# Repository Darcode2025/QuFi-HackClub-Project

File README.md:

# QuFi-HackClub-Project
This is a macropad specifically designed for excel shortcuts for accounting in public companies and private companies. Its more relevant for public companies who have to track and show certain data to shareholders.

# QuFi

### **A custom macropad that simplifies accounting and financial analysis.**
---

# What Is This? 

**QuFi** is a macropad that brings some of the most commonly used financial formulas into excel with no technical experience
required. It uniquely offers both commonly used preloaded formulas, as well as customizable layers in a library of financial formulas or you can bring your own formulas! 

- **GAAP Accounting Formulas:** QuFi Comes preloaded with 27 GAAP Accounting formulas with everything from calculating assets to Income Calculations
- **Full Customizable Library:** I'm currently working on a libarary to bring almost any excel accounting or corporate finance formula to QuFi which will allow users the change their configurationa and quick formulas.
- **Custom Formulas:** I'm working on documentation for users to create their own formulas either by themselves or using AI to apply to QuFi.

## Key Layout

| Key | Action | Shortcut Sent |
|-----|--------|---------------|
| 1 | Accounting equation check (should equal 0) | =Assets-(Liabilities+Equity) |
| 2 |Gross profit | =Revenue-COGS |
| 3 | Net income | 	=Revenue-Expenses |
| 4 | Gross margin % | =(Revenue-COGS)/Revenue |
| 5 | Working capital | =CurrentAssets-CurrentLiabilities |
| 6 | Current ratio| =(Cash+AR+Securities)/CurrentLiabilities |
| 7 | Quick ratio | 	=Revenue-Expenses |
| 8 | Debt-to-equity | =TotalLiabilities/TotalEquity |
| 9 | Straight-line depreciation | =SLN(Cost,Salvage,Life) |
---

# How To Use It

1. Plug it into your computer via USB-C.
2. Firmware is being developed
3. Open Excel and press any key.
4. Command changed in firmware are being developed.
5. To directly select numbers used in the formula, click equals in the cell which the desired output should reside in, then click on all the relevant data in order they show up in the equation, then click the key on QuFi

---

# Why I Made This

My Parents are in corporate finance, and I suprisingly love investing and financial analysis. I see them every day using excel and related platforms and its genuinly a typing strain. I've personally used it many times as well 
and it is still efficient but it can be easier and quicker.

---

# Images

## Full 3D Model without keycaps and knob (Assembled)

## PCB

## Schematic

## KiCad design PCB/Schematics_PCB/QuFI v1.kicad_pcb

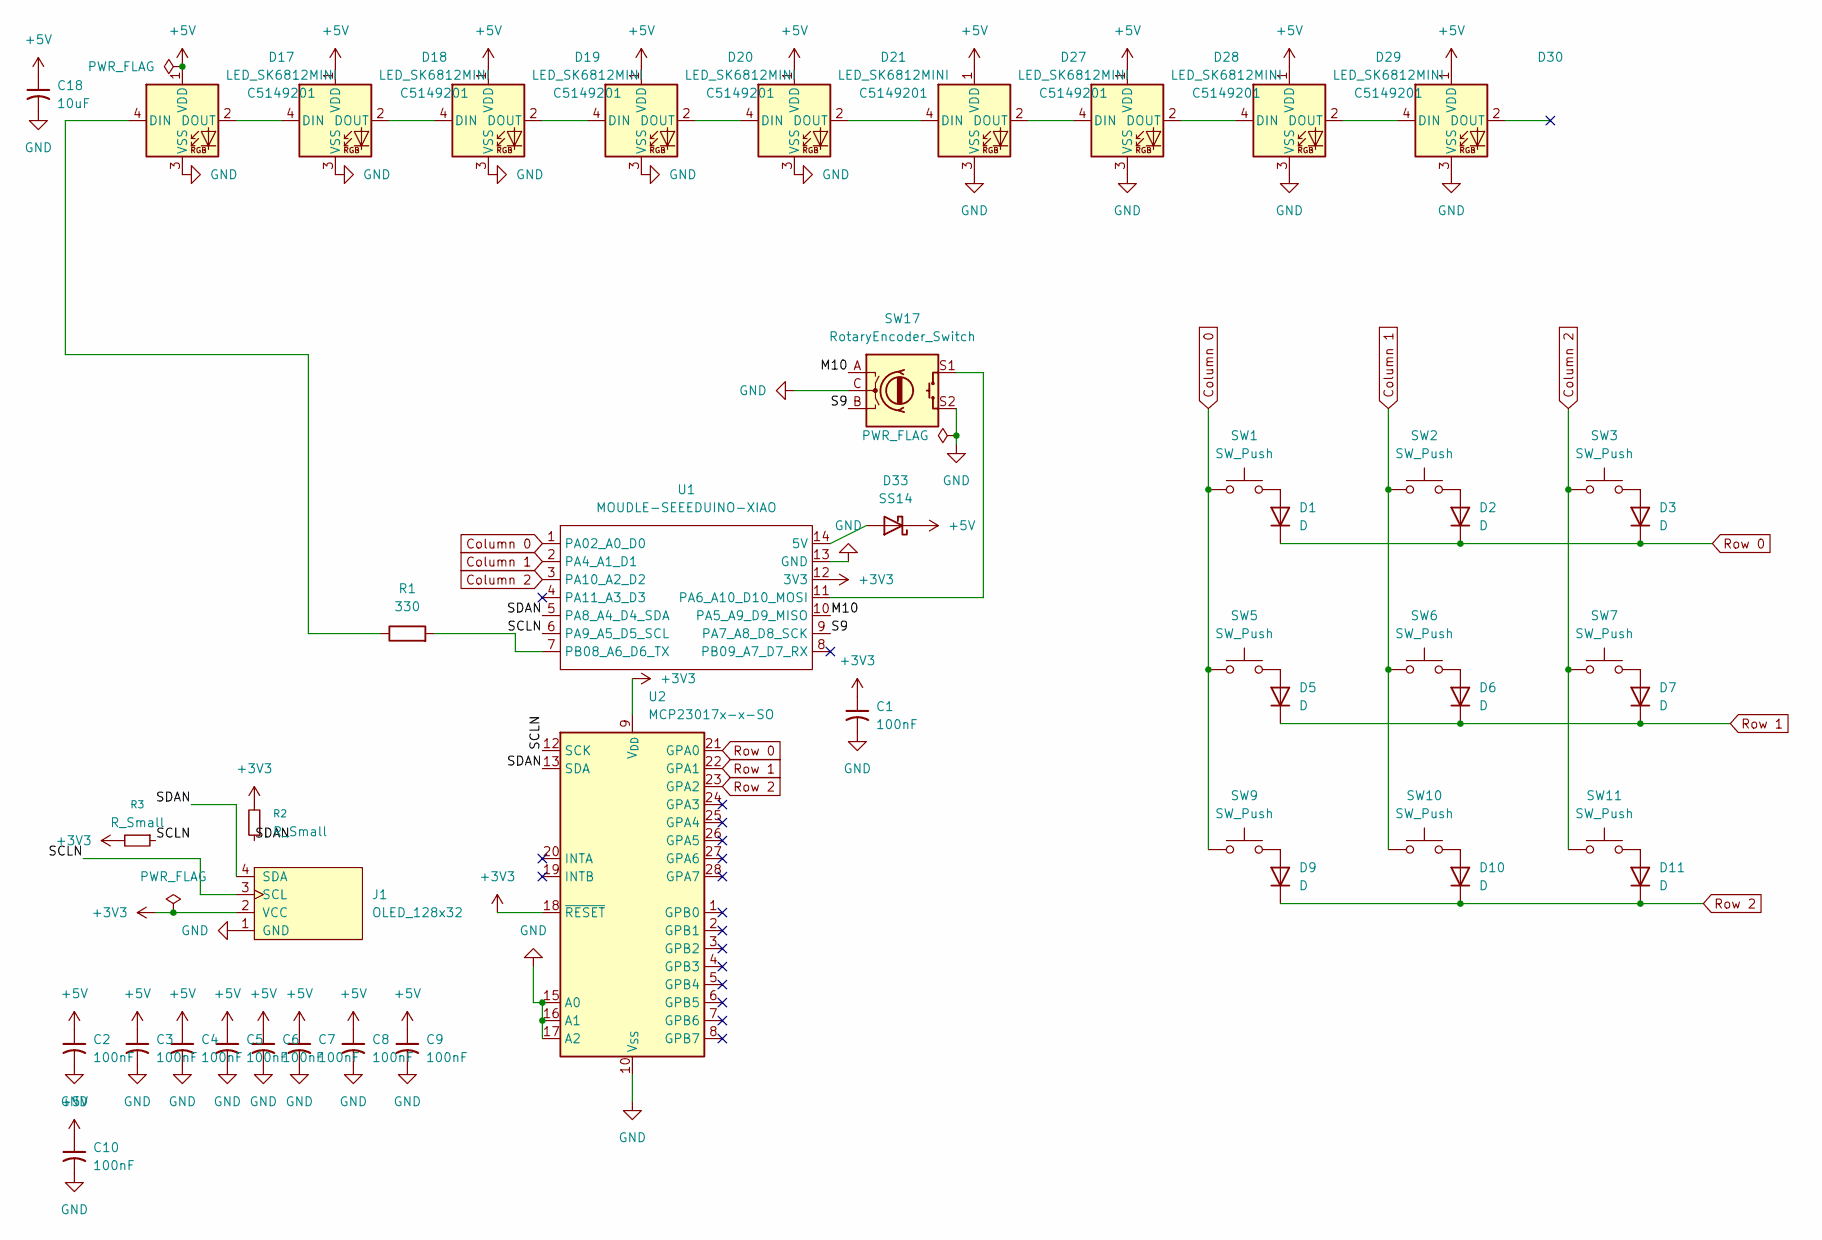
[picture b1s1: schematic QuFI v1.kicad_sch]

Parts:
C1, C2, C3, C4, C5, C6, C7, C8, C9, C10: 100nF; C_0805_2012Metric_Pad1.18x1.45mm_HandSolder
C18: 10uF; C_1206_3216Metric_Pad1.33x1.80mm_HandSolder
D1, D2, D3, D5, D6, D7, D9, D10, D11: D; Diode_DO-35
D17, D18, D19, D20, D21, D27, D28, D29, D30: LED_SK6812MINI; LCSC C5149201
D33: SS14; D_SMA_Handsoldering
J1: OLED_128x32
R1: 330; R_0805_2012Metric_Pad1.20x1.40mm_HandSolder
R2, R3: R_Small; R_0805_2012Metric_Pad1.20x1.40mm_HandSolder
SW1, SW2, SW3, SW5, SW6, SW7, SW9, SW10, SW11: SW_Push; MX_PCB_1.00u
SW17: RotaryEncoder_Switch; RotaryEncoder_Alps_EC11E-Switch_Vertical_H20mm
U1: MOUDLE-SEEEDUINO-XIAO; XIAO-RP2040-SMD-V2
U2: MCP23017x-x-SO; SOIC-28W_7.5x17.9mm_P1.27mm

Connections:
+3V3: C1.1, J1.2 (VCC), R2.2, R3.2, U1.12 (3V3), U2.9 (V_{DD}), U2.18 (~RESET)
+5V: C2.1, C3.1, C4.1, C5.1, C6.1, C7.1, C8.1, C9.1, C10.1, C18.1, D17.1 (VDD), D18.1 (VDD), D19.1 (VDD), D20.1 (VDD), D21.1 (VDD), D27.1 (VDD), D28.1 (VDD), D29.1 (VDD), D30.1 (VDD), D33.1 (K)
/M10: SW17.A, U1.10 (PA5_A9_D9_MISO)
/S9: SW17.B, U1.9 (PA7_A8_D8_SCK)
/SCLN: J1.3 (SCL), R3.1, U1.6 (PA9_A5_D5_SCL), U2.12 (SCK)
/SDAN: J1.4 (SDA), R2.1, U1.5 (PA8_A4_D4_SDA), U2.13 (SDA)
Column 0: SW1.1, SW5.1, SW9.1, U1.1 (PA02_A0_D0)
Column 1: SW2.1, SW6.1, SW10.1, U1.2 (PA4_A1_D1)
Column 2: SW3.1, SW7.1, SW11.1, U1.3 (PA10_A2_D2)
GND: C1.2, C2.2, C3.2, C4.2, C5.2, C6.2, C7.2, C8.2, C9.2, C10.2, C18.2, D17.3 (VSS), D18.3 (VSS), D19.3 (VSS), D20.3 (VSS), D21.3 (VSS), D27.3 (VSS), D28.3 (VSS), D29.3 (VSS), D30.3 (VSS), J1.1 (GND), SW17.C, SW17.S2, U1.13 (GND), U2.10 (V_{SS}), U2.15 (A0), U2.16 (A1), U2.17 (A2)
unnamed: D1.2 (A), SW1.2
unnamed: D2.2 (A), SW2.2
unnamed: D3.2 (A), SW3.2
unnamed: D5.2 (A), SW5.2
unnamed: D6.2 (A), SW6.2
unnamed: D7.2 (A), SW7.2
unnamed: D9.2 (A), SW9.2
unnamed: D10.2 (A), SW10.2
unnamed: D11.2 (A), SW11.2
unnamed: D17.4 (DIN), R1.1
unnamed: D17.2 (DOUT), D18.4 (DIN)
unnamed: D18.2 (DOUT), D19.4 (DIN)
unnamed: D19.2 (DOUT), D20.4 (DIN)
unnamed: D20.2 (DOUT), D21.4 (DIN)
unnamed: D21.2 (DOUT), D27.4 (DIN)
unnamed: D27.2 (DOUT), D28.4 (DIN)
unnamed: D28.2 (DOUT), D29.4 (DIN)
unnamed: D29.2 (DOUT), D30.4 (DIN)
unnamed: D33.2 (A), U1.14 (5V)
unnamed: SW17.S1, U1.11 (PA6_A10_D10_MOSI)
unnamed: R1.2, U1.7 (PB08_A6_D6_TX)
Row 0: D1.1 (K), D2.1 (K), D3.1 (K), U2.21 (GPA0)
Row 1: D5.1 (K), D6.1 (K), D7.1 (K), U2.22 (GPA1)
Row 2: D9.1 (K), D10.1 (K), D11.1 (K), U2.23 (GPA2)

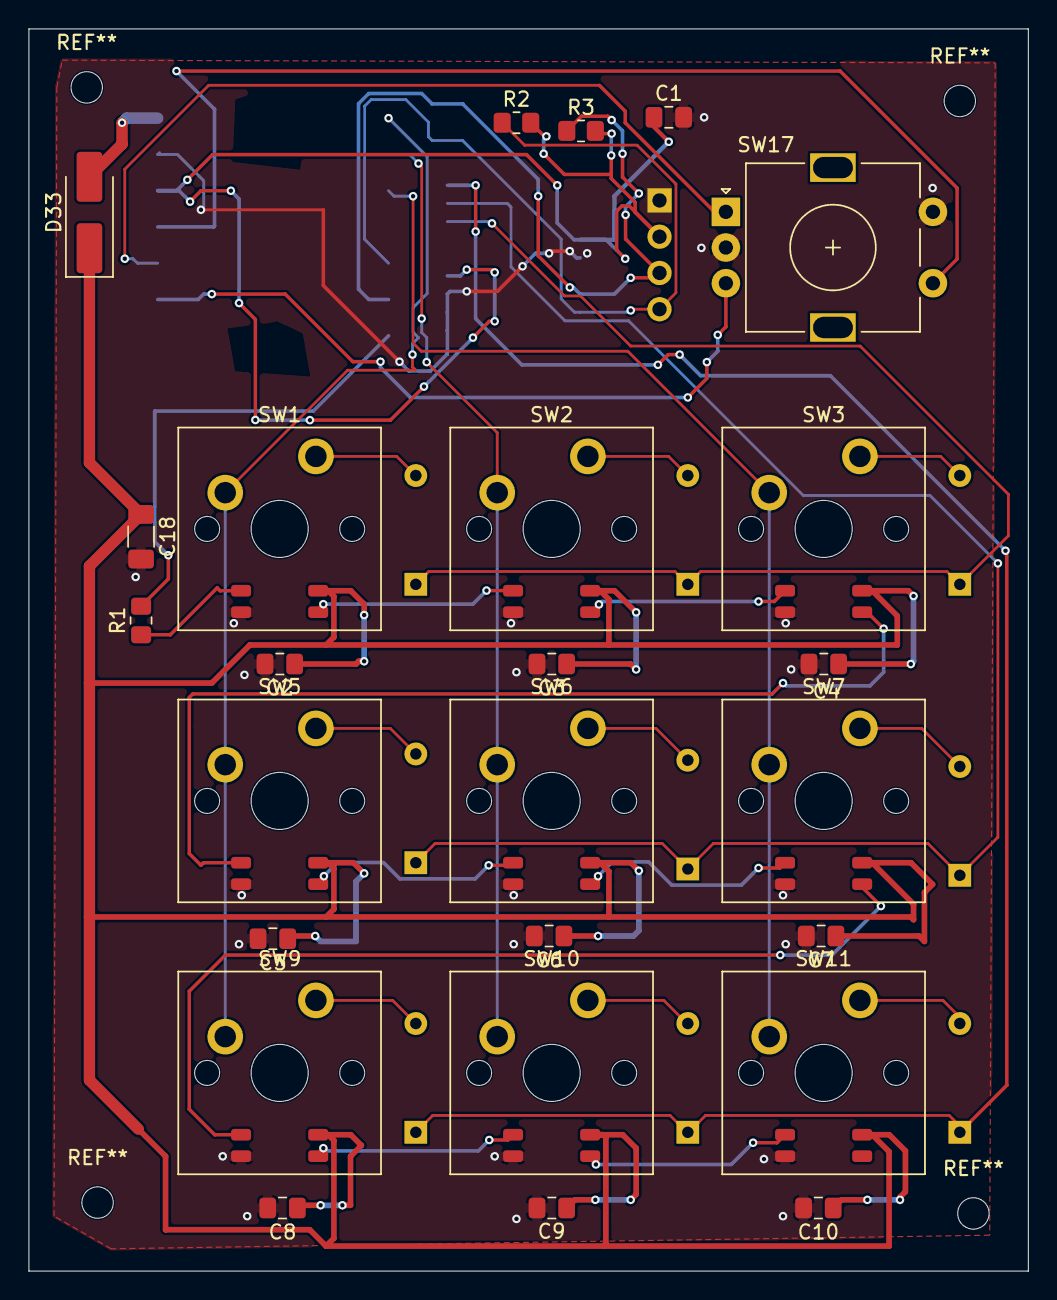
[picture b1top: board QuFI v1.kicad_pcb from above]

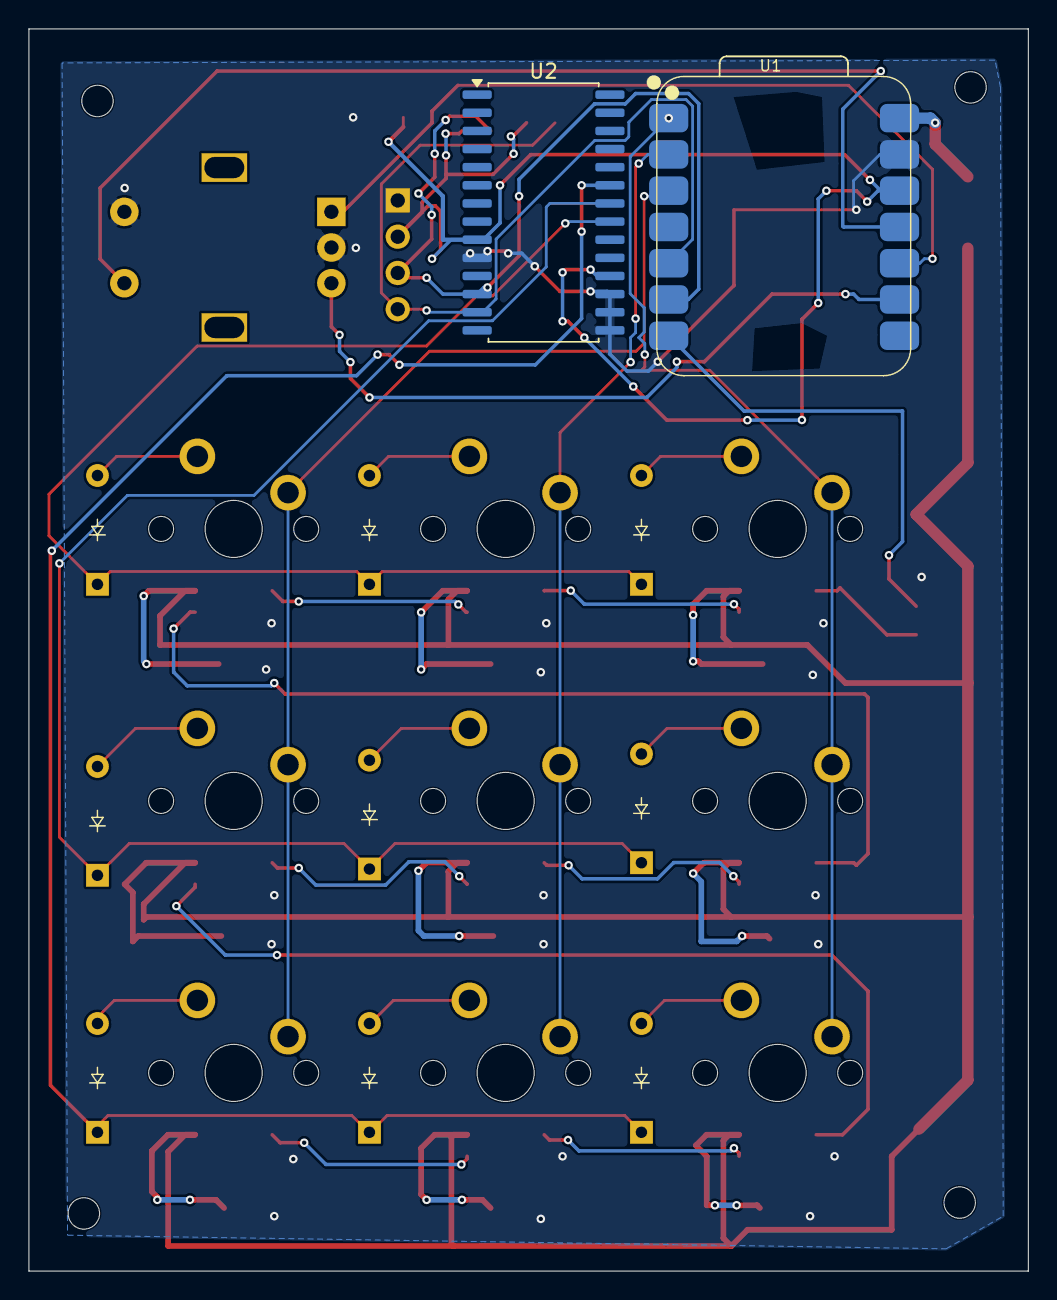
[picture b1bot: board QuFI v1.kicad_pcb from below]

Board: 2 copper layers, 70.0 x 87.0 mm, 46 parts (11 on the bottom side), 34 nets.
